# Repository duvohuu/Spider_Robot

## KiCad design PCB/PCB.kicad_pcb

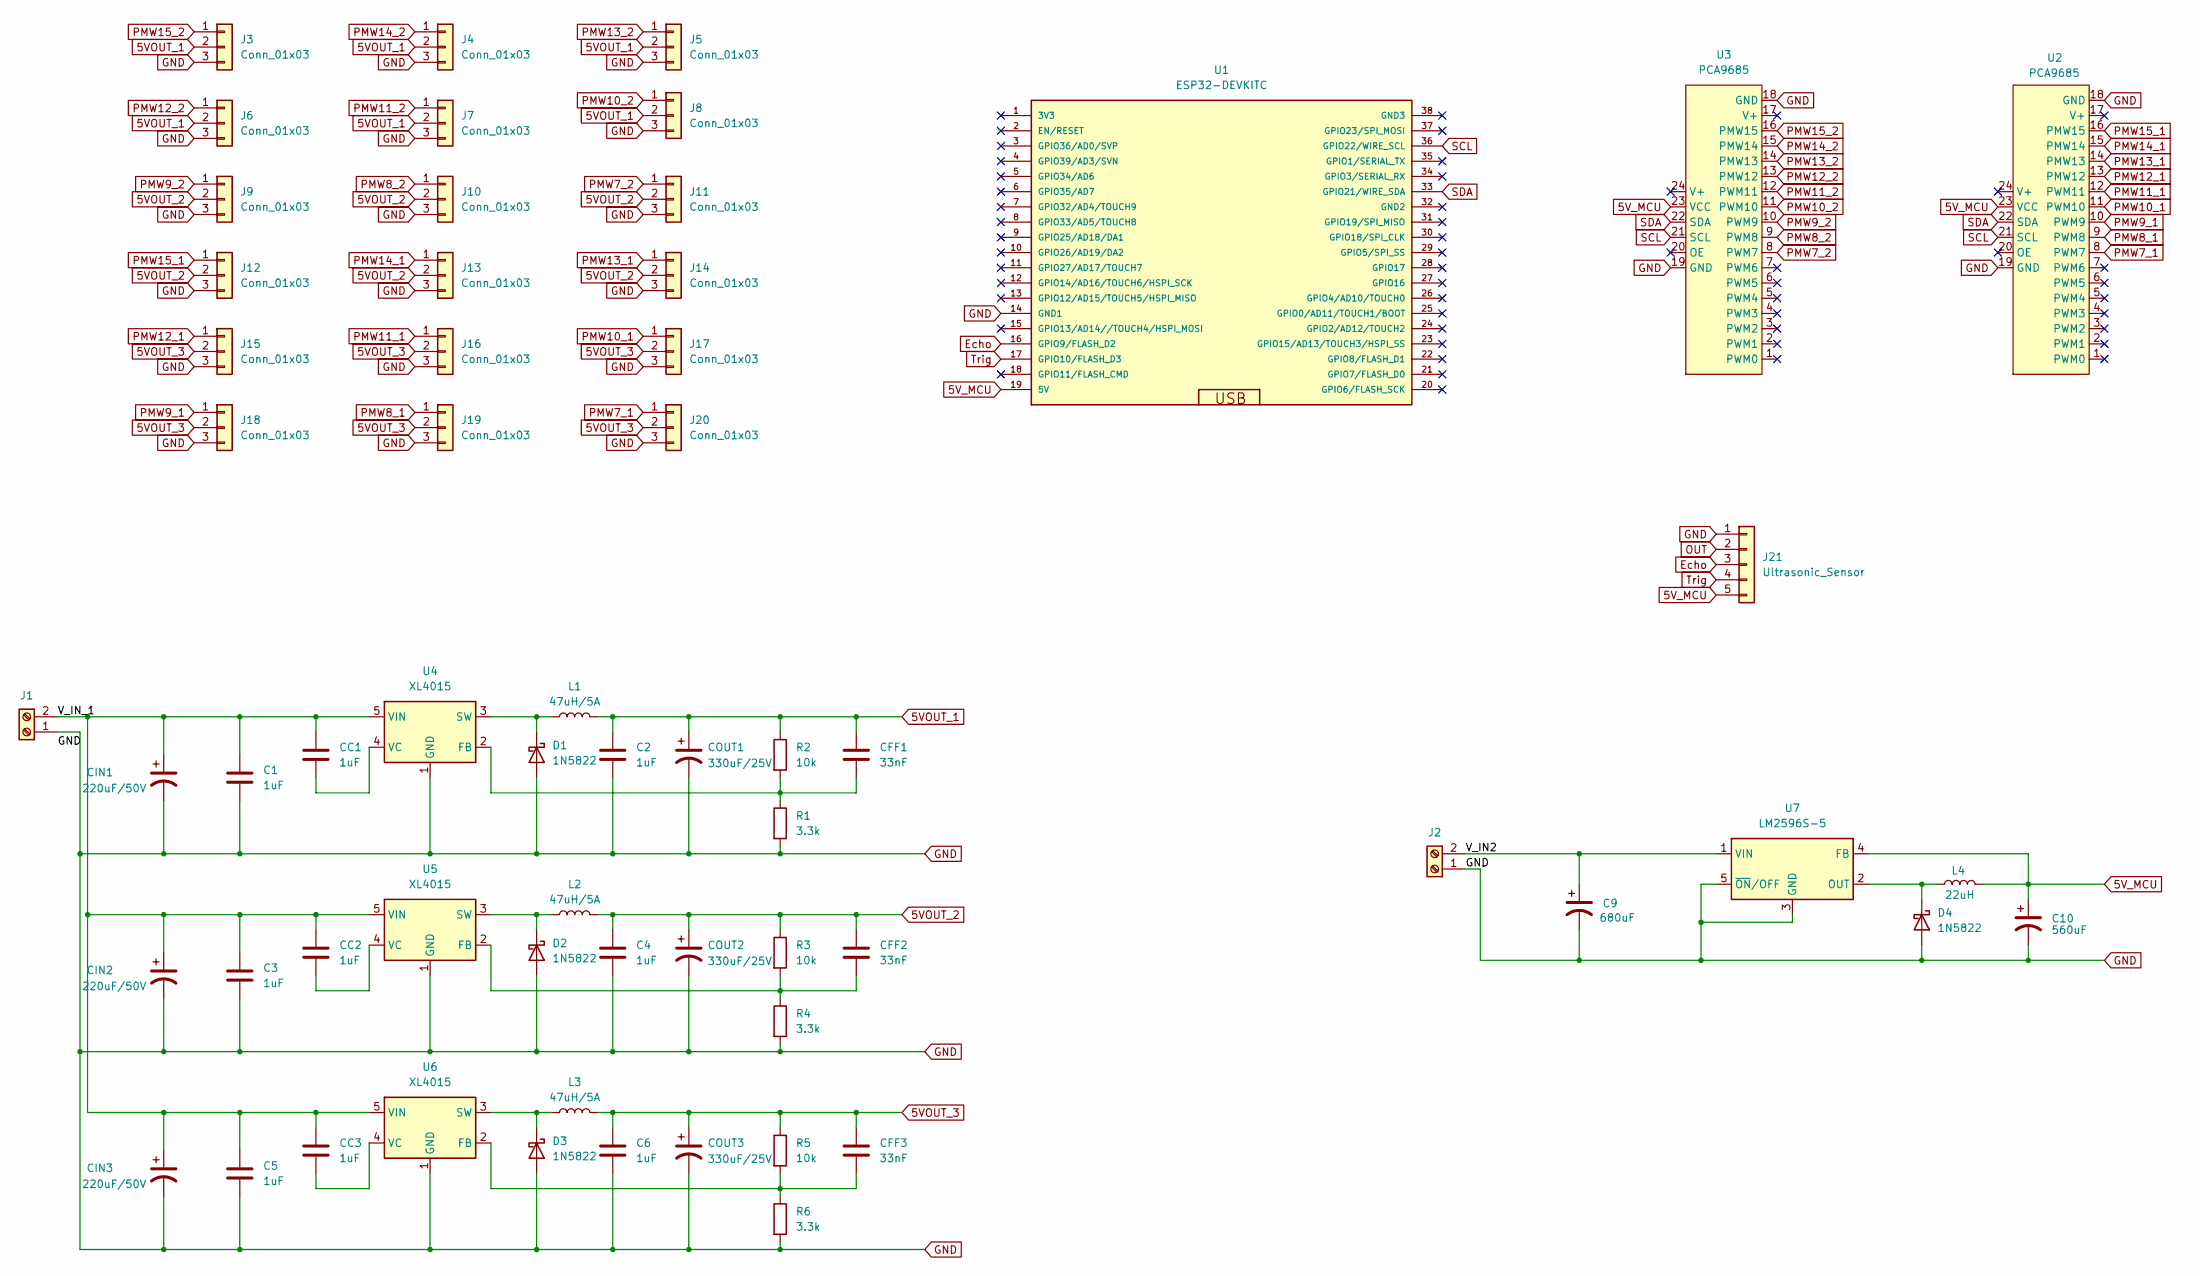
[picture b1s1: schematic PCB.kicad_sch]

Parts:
C1, C2, C3, C4, C5, C6: 1uF; C_0603_1608Metric_Pad1.08x0.95mm_HandSolder
C9: 680uF; CP_Radial_D8.0mm_P5.00mm
C10: 560uF; CP_Radial_D8.0mm_P5.00mm
CC1, CC2, CC3: 1uF; C_0603_1608Metric_Pad1.08x0.95mm_HandSolder
CFF1, CFF2, CFF3: 33nF; C_0603_1608Metric_Pad1.08x0.95mm_HandSolder
CIN1, CIN2, CIN3: 220uF/50V; CP_Radial_D8.0mm_P5.00mm
COUT1, COUT2, COUT3: 330uF/25V; CP_Radial_D8.0mm_P5.00mm
D1, D2, D3, D4: 1N5822; D_SMA_Handsoldering
J1, J2: MCU POWER; TerminalBlock_MaiXu_MX126-5.0-02P_1x02_P5.00mm
J3, J4, J5, J6, J7, J8, J9, J10, J11, J12, J13, J14, J15, J16, J17, J18, J19, J20: Conn_01x03; PinHeader_1x03_P2.54mm_Vertical
J21: Ultrasonic_Sensor; PinHeader_1x05_P2.54mm_Vertical
L1, L2, L3: 47uH/5A; L_12x12mm_H8mm
L4: 22uH; L_12x12mm_H8mm
R1, R4, R6: 3.3k; R_Axial_DIN0207_L6.3mm_D2.5mm_P7.62mm_Horizontal
R2, R3, R5: 10k; R_Axial_DIN0207_L6.3mm_D2.5mm_P7.62mm_Horizontal
U1: ESP32-DEVKITC
U2, U3: PCA9685
U4, U5, U6: XL4015; TO-263-5_TabPin3
U7: LM2596S-5; TO-263-5_TabPin3

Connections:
5VOUT_1: C2.1, CFF1.1, COUT1.1, J3.2, J4.2, J5.2, J6.2, J7.2, J8.2, L1.2, R2.1
5VOUT_2: C4.1, CFF2.1, COUT2.1, J9.2, J10.2, J11.2, J12.2, J13.2, J14.2, L2.2, R3.1
5VOUT_3: C6.1, CFF3.1, COUT3.1, J15.2, J16.2, J17.2, J18.2, J19.2, J20.2, L3.2, R5.1
5V_MCU: C10.1, J21.5, L4.2, U1.19 (5V), U2.23 (VCC), U3.23 (VCC), U7.4 (FB)
/V_IN2: C9.1, J2.2, U7.1 (VIN)
/V_IN_1: C1.1, C3.1, C5.1, CC1.1, CC2.1, CC3.1, CIN1.1, CIN2.1, CIN3.1, J1.2, U4.5 (VIN), U5.5 (VIN), U6.5 (VIN)
Echo: J21.3, U1.16 (GPIO9/FLASH_D2)
GND: C1.2, C2.2, C3.2, C4.2, C5.2, C6.2, C9.2, C10.2, CIN1.2, CIN2.2, CIN3.2, COUT1.2, COUT2.2, COUT3.2, D1.2 (A), D2.2 (A), D3.2 (A), D4.2 (A), J1.1, J2.1, J3.3, J4.3, J5.3, J6.3, J7.3, J8.3, J9.3, J10.3, J11.3, J12.3, J13.3, J14.3, J15.3, J16.3, J17.3, J18.3, J19.3, J20.3, J21.1, R1.2, R4.2, R6.2, U1.14 (GND1), U2.18 (GND), U2.19 (GND), U3.18 (GND), U3.19 (GND), U4.1 (GND), U5.1 (GND), U6.1 (GND), U7.3 (GND), U7.5 (~ON/OFF)
unnamed: D1.1 (K), L1.1, U4.3 (SW)
unnamed: D2.1 (K), L2.1, U5.3 (SW)
unnamed: D3.1 (K), L3.1, U6.3 (SW)
unnamed: D4.1 (K), L4.1, U7.2 (OUT)
unnamed: CFF1.2, R1.1, R2.2, U4.2 (FB)
unnamed: CC1.2, U4.4 (VC)
unnamed: CFF2.2, R3.2, R4.1, U5.2 (FB)
unnamed: CC2.2, U5.4 (VC)
unnamed: CFF3.2, R5.2, R6.1, U6.2 (FB)
unnamed: CC3.2, U6.4 (VC)
OUT: J21.2
PMW7_1: J20.1, U2.8 (PWM7)
PMW7_2: J11.1, U3.8 (PWM7)
PMW8_1: J19.1, U2.9 (PWM8)
PMW8_2: J10.1, U3.9 (PWM8)
PMW9_1: J18.1, U2.10 (PWM9)
PMW9_2: J9.1, U3.10 (PWM9)
PMW10_1: J17.1, U2.11 (PWM10)
PMW10_2: J8.1, U3.11 (PWM10)
PMW11_1: J16.1, U2.12 (PWM11)
PMW11_2: J7.1, U3.12 (PWM11)
PMW12_1: J15.1, U2.13 (PMW12)
PMW12_2: J6.1, U3.13 (PMW12)
PMW13_1: J14.1, U2.14 (PMW13)
PMW13_2: J5.1, U3.14 (PMW13)
PMW14_1: J13.1, U2.15 (PMW14)
PMW14_2: J4.1, U3.15 (PMW14)
PMW15_1: J12.1, U2.16 (PMW15)
PMW15_2: J3.1, U3.16 (PMW15)
SCL: U1.36 (GPIO22/WIRE_SCL), U2.21 (SCL), U3.21 (SCL)
SDA: U1.33 (GPIO21/WIRE_SDA), U2.22 (SDA), U3.22 (SDA)
Trig: J21.4, U1.17 (GPIO10/FLASH_D3)

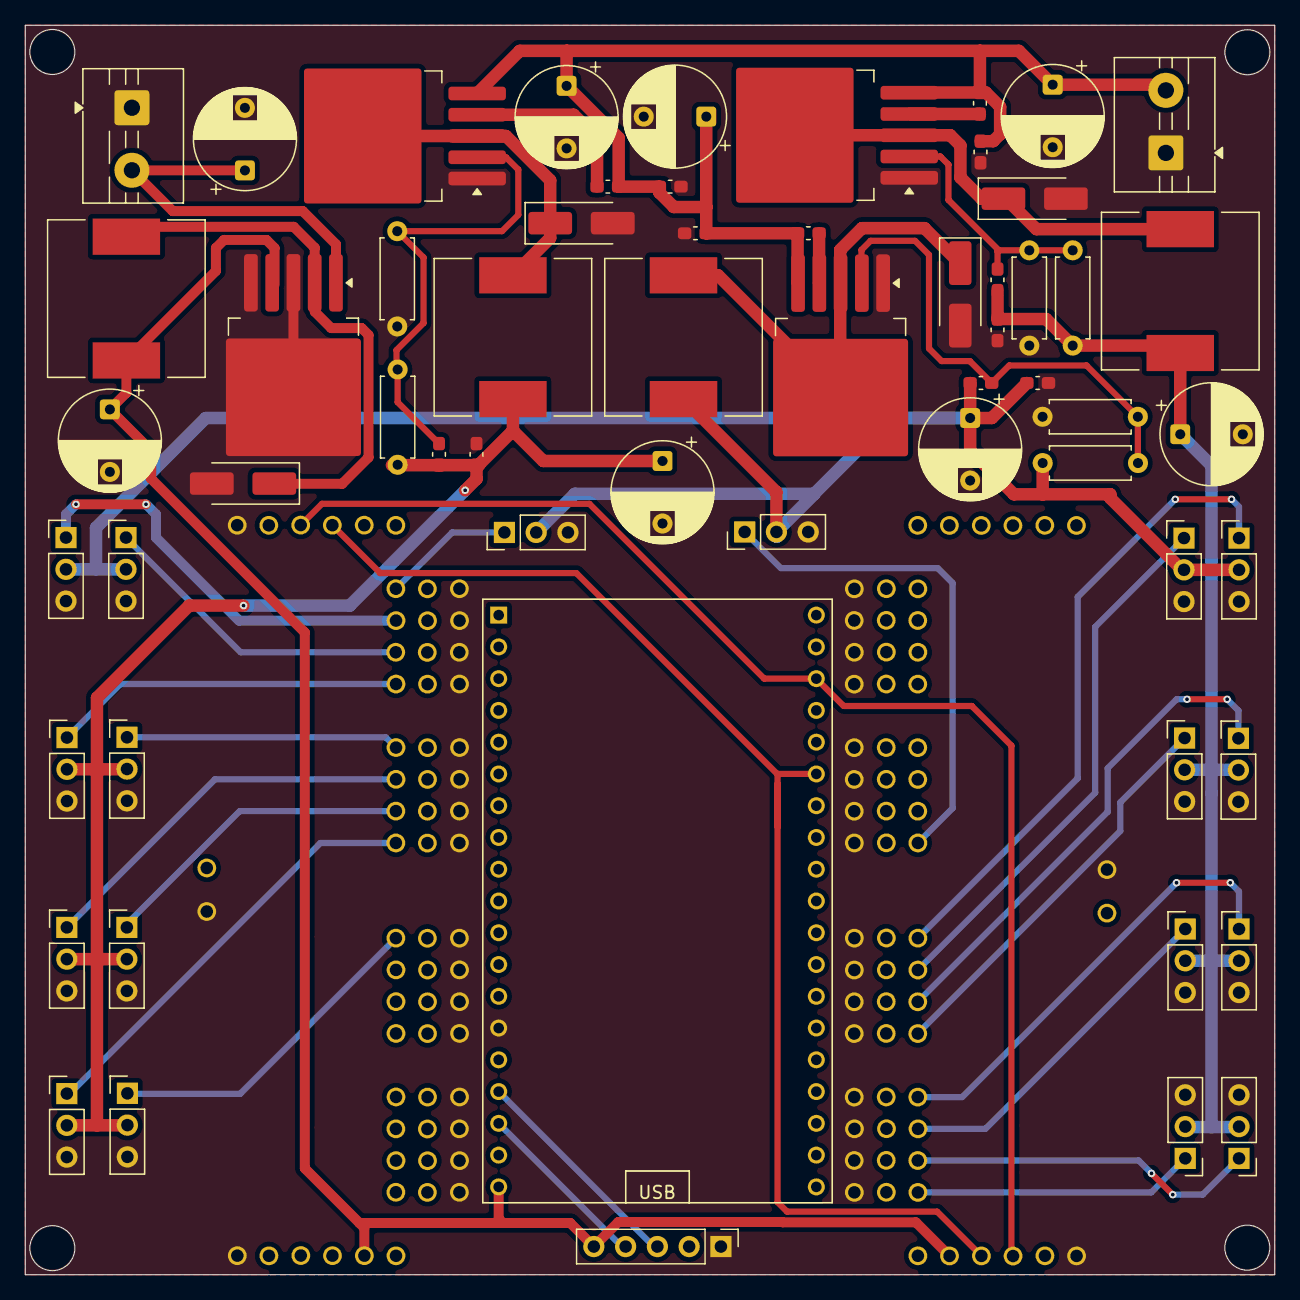
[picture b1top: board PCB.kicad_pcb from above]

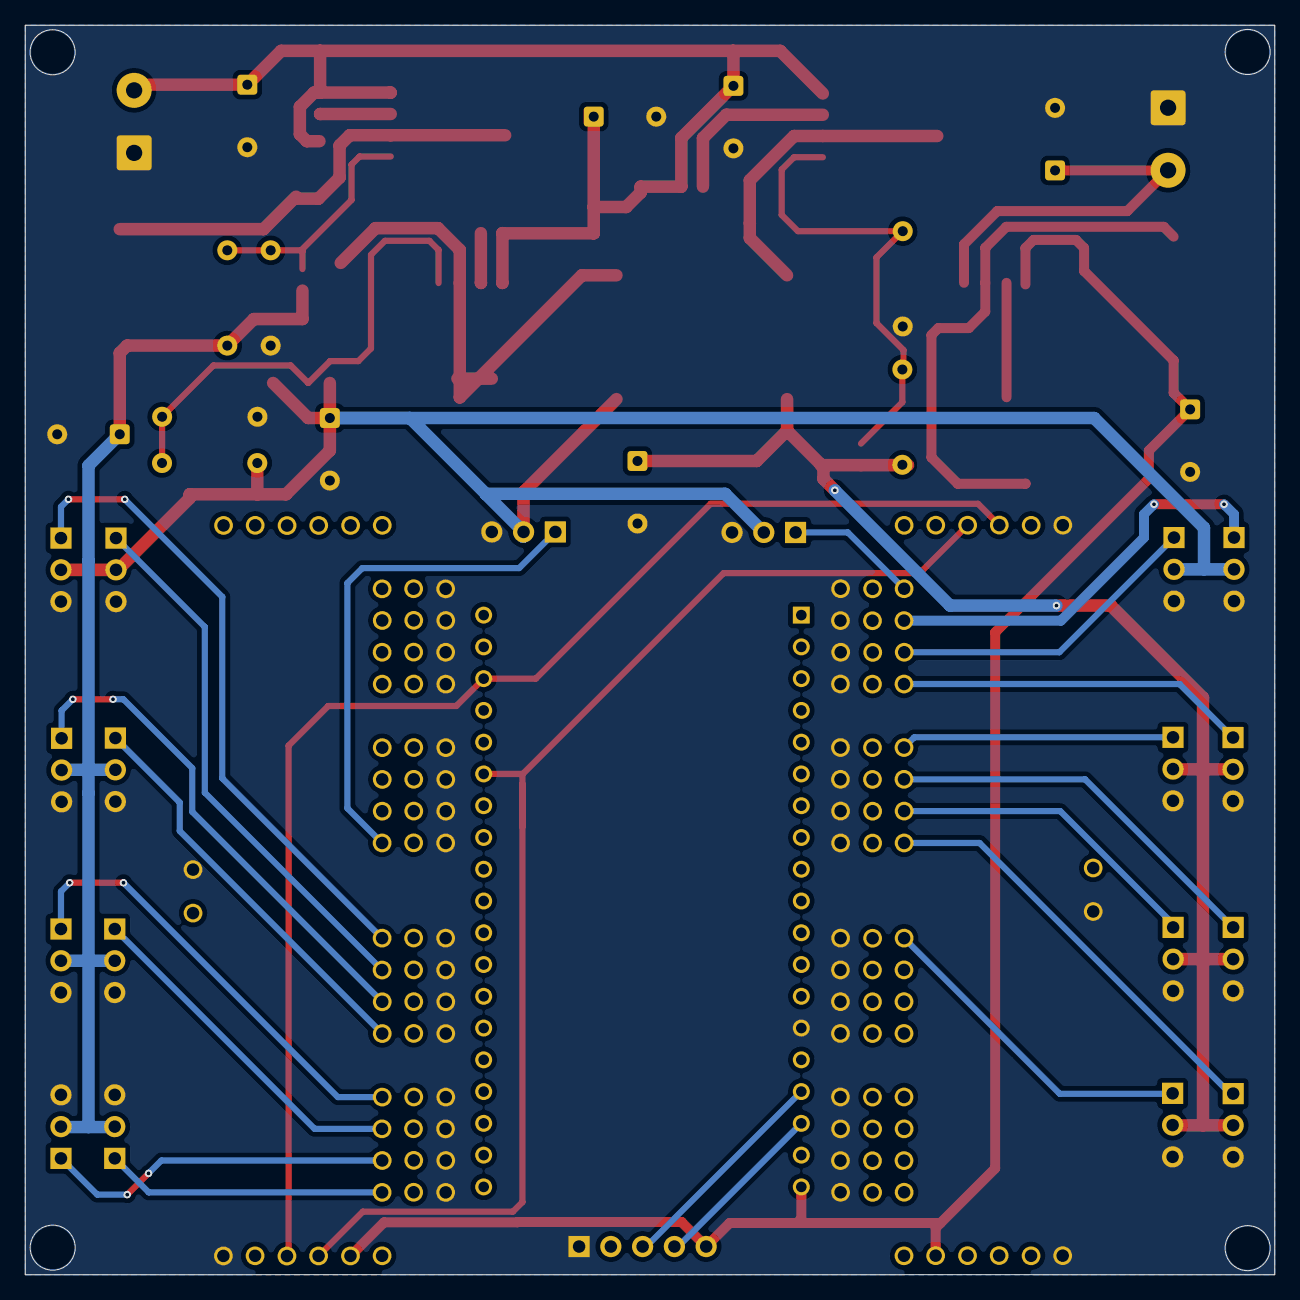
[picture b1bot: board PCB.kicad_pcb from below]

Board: 2 copper layers, 99.9 x 99.9 mm, 62 parts (2 on the bottom side), 39 nets.

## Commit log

2026-03-12 Init Project
2026-03-30 Update code folder
2026-04-24 Update Hardware PCB
2026-04-25 Move forward updating
2026-05-05 Add latex template and stand mode for robot
2026-05-05 Add Latex chapter 1->4
2026-05-05 Change latex folder name
2026-05-05 Remove .vscode/ folder
2026-05-05 Add inverse kinematic of robot
2026-05-06 Refactor code
2026-05-09 Add Web/app demo for robot
2026-05-10 Change STAND_X to runtime variable
2026-05-10 Add HY-SRF05
2026-05-12 Complete Project
2026-05-16 Add slide latex
2026-05-17 Complete Slide
